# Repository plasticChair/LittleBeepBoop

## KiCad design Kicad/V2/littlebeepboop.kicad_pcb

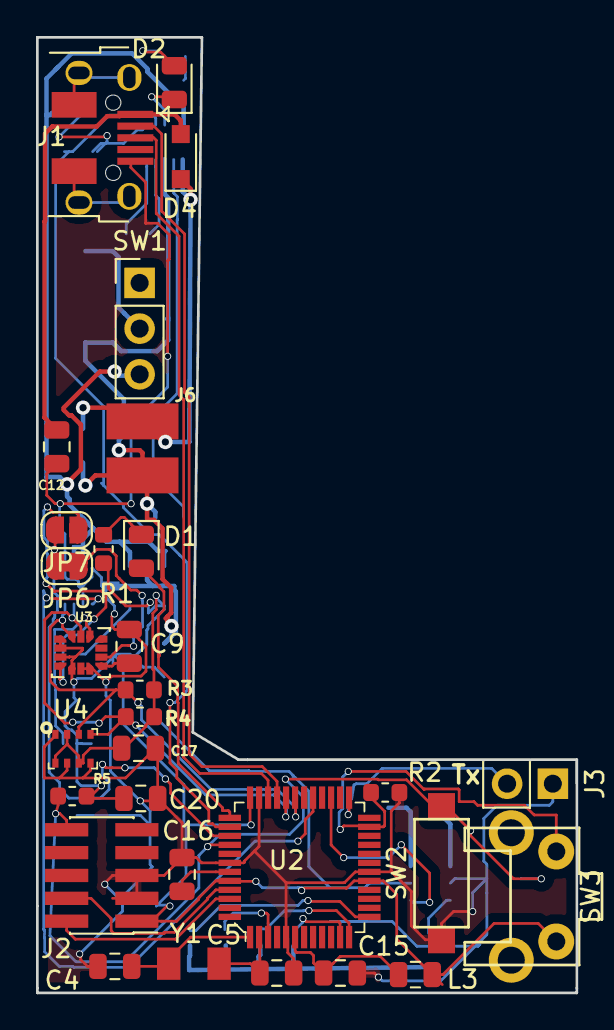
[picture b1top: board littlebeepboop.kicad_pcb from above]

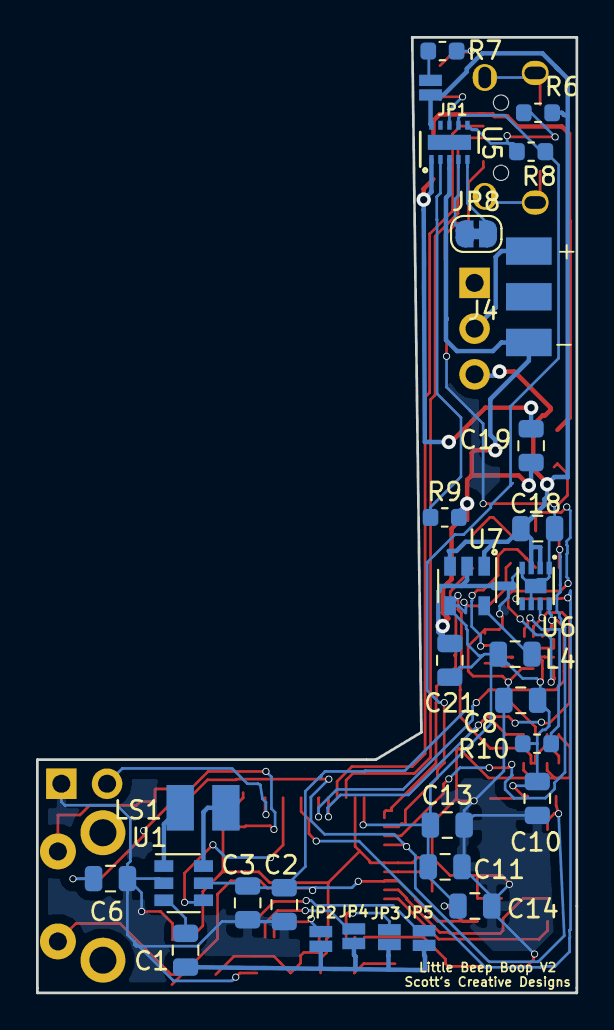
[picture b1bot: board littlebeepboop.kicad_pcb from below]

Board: 2 copper layers, 30.0 x 53.1 mm, 61 parts (31 on the bottom side), 46 nets.

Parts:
C1, C2, C3, C4, C5, C21: C; C_0805_2012Metric
C6, C10, C13, C14, C15, C16: 82n; C_0805_2012Metric
C8, C9, C12, C17, C20: 100nF; C_0805_2012Metric
C11: 2.2u; C_0805_2012Metric
C18, C19: 0.1uF; C_0805_2012Metric
D1: LED_B; LED_0805_2012Metric
D2: LED; LED_0805_2012Metric
D4: D; D_SOD-323_HandSoldering
J1: USB_B_Micro; USB_Micro-B_Adafruit
J2: Conn_ARM_JTAG_SWD_10; PinHeader_2x05_P1.27mm_Vertical_SMD
J3: Conn_01x02; PinHeader_1x02_P2.54mm_Vertical
J4: Conn_01x03; SMD_3Pin_2.54mm
J6: Conn_01x02; 2_PIN_SMD
JP1: J_NO; SMT-JUMPER_2_NO_NO-SILK
JP2, JP3, JP4, JP5: Jmp_NO; SMT-JUMPER_2_NO_NO-SILK
JP6: NC; SolderJumper-2_P1.3mm_Bridged_RoundedPad1.0x1.5mm
JP7: NO; SolderJumper-2_P1.3mm_Open_RoundedPad1.0x1.5mm
JP8: Jumper_NC_Small; SolderJumper-2_P1.3mm_Bridged_RoundedPad1.0x1.5mm
L3, L4: INDUCTOR; L_0805_2012Metric
LS1: Speaker; CMS-151125-078X
NT2: Net-Tie_2; NetTie-2_SMD_Pad0.5mm
R1: 5.6; R_0603_1608Metric
R2, R5, R6, R8, R10: 10k; R_0603_1608Metric
R3, R4: R; R_0603_1608Metric
R7: 330; R_0603_1608Metric
R9: 750; R_0603_1608Metric
SW1: SW_SPDT; PinHeader_1x03_P2.54mm_Vertical
SW2: Switch; Tact_SMD_Switch
SW3: Switch; ebay_RA_Mom_switch
U1: PAM8301; SOT-23-6
U2: ATSAMD21G18A-AUT; TQFP-48_7x7mm
U3: LSM6DS3; LGA-14_3x2.5mm_P0.5mm_LayoutBorder3x4y
U4: BMP280; LGA-8_2x2.5mm_BMP280
U5: BQ24210; WSON-10-1EP_2x3mm_P0.5mm_EP0.84x2.4mm
U6: MAX17048; TQFN-8_2x2x0.75
U7: LM3671; SOT-23-5
Y1: Crystal; TFE322P32K7680R

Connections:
/BatteryManagement/Batt-: C19.2, C21.2, J4.1, J6.2, NT2.1, R9.2, U5.3, U7.2
/BatteryManagement/Batt_int: J4.3, SW1.2
/BatteryManagement/Solar+: C19.1, D4.1, J6.1, U5.1
/RESET: C6.1, J2.10, R5.1, SW2.1, U2.40
/SWDCLK: J2.4, U2.45
/SWDIO: J2.2, U2.46
/USB_DM: J1.2, U2.33
/USB_DP: J1.3, U2.34
/VDDANA: C15.1, L3.2, U2.6
/VDDCORE: C16.1, U2.43
Audio: C1.1, JP2.1, JP3.1, JP4.1, JP5.1
BATT_ALRT: U2.29, U6.5
BattPwr: C18.2, JP1.1, R6.1, SW1.3, U5.10, U6.2, U6.3, U7.1, U7.3
BattRtn: C2.2, C3.2, C4.1, C5.1, C6.2, C8.2, C9.2, C10.2, C11.2, C12.1, C13.2, C14.2, C15.2, C16.2, C17.2, C18.1, C20.2, J1.5, J2.3, J2.5, J3.1, NT2.2, R2.2, SW2.2, U1.2, U2.5, U2.18, U2.35, U2.42, U3.6, U3.7, U4.1, U4.5, U4.7, U6.1, U6.4, U6.6, U6.9
CHRG_EN: R8.2, U2.38, U5.7
Fun_Btn_1_P23: R2.1, SW3.2, U2.23
IMU_INT: JP6.2, JP7.2, U2.39
LED1_P2: D1.2, U2.37
unnamed: C1.2, U1.3
unnamed: C4.2, U2.1, Y1.1
unnamed: C5.2, U2.2, Y1.2
unnamed: C9.1, U3.8
unnamed: D1.1, R1.1
unnamed: D2.1, U5.8
unnamed: D2.2, R7.2
unnamed: J3.2, U2.25
unnamed: JP1.2, R7.1
unnamed: JP2.2, U2.11
unnamed: JP3.2, U2.3
unnamed: JP4.2, U2.12
unnamed: JP5.2, U2.13
unnamed: JP6.1, U3.9
unnamed: JP7.1, U3.4
unnamed: JP8.1, U5.4
unnamed: JP8.2, U5.5
unnamed: L4.1, U7.5
unnamed: LS1.1, U1.6
unnamed: LS1.2, U1.1
unnamed: R6.2, R8.1, U5.6
unnamed: R9.1, U5.2
unnamed: R10.2, U3.12
SCL: R4.2, U2.32, U3.13, U4.4, U6.7
SDA: R3.2, U2.31, U3.14, U4.3, U6.8
Shutdown: U1.4, U2.27
USB_PWR: C12.2, D4.2, J1.1
Vdd: C2.1, C3.1, C8.1, C10.1, C11.1, C13.1, C14.1, C17.1, C20.1, C21.1, J2.1, L3.1, L4.2, R1.2, R3.1, R4.1, R5.2, R10.1, SW3.1, U1.5, U2.17, U2.36, U2.44, U3.1, U3.2, U3.3, U3.5, U4.2, U4.6, U4.8, U7.4

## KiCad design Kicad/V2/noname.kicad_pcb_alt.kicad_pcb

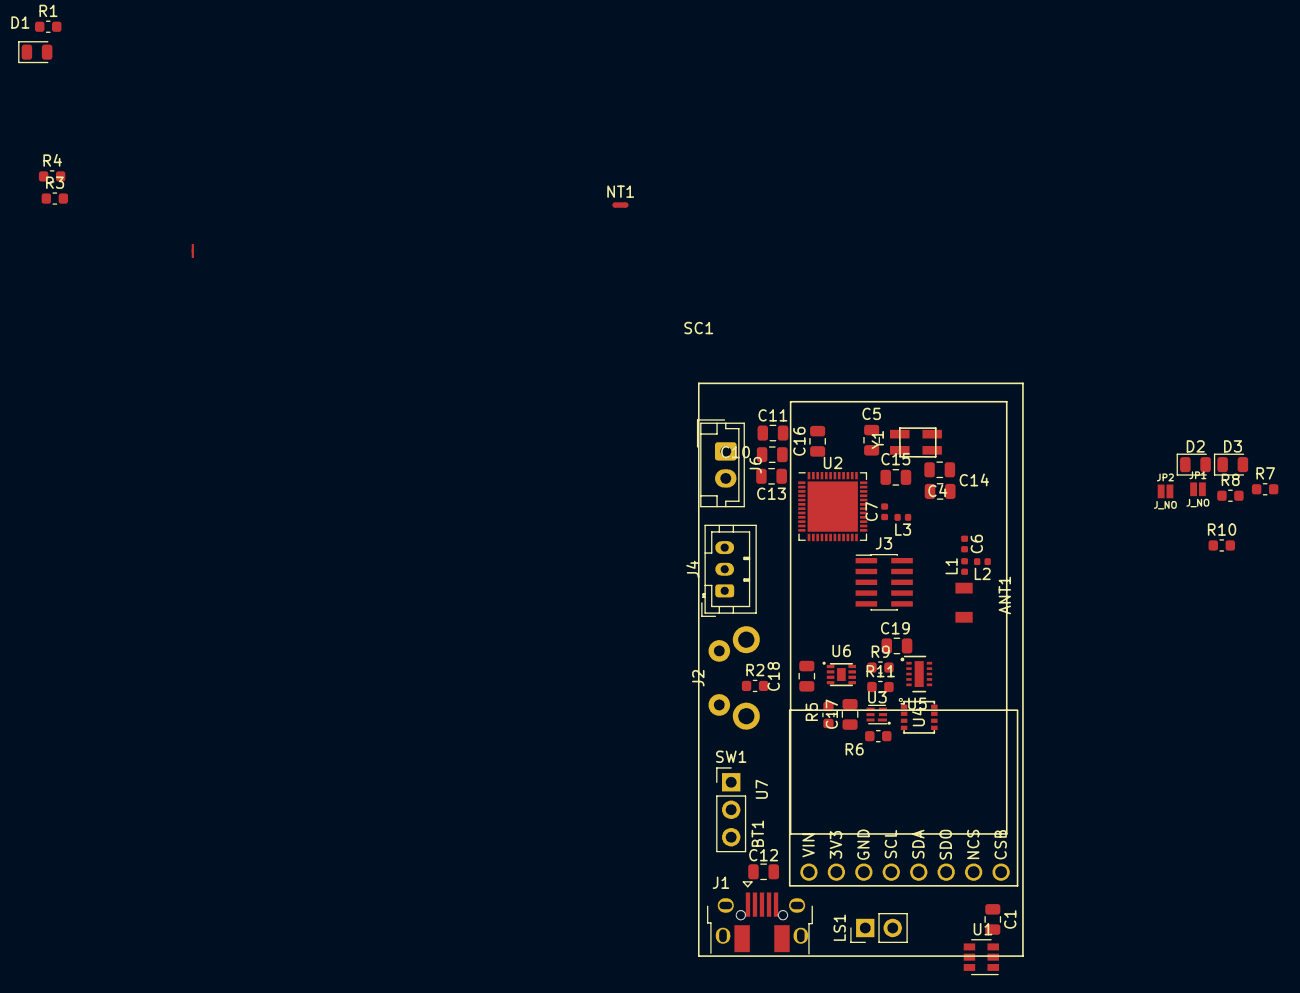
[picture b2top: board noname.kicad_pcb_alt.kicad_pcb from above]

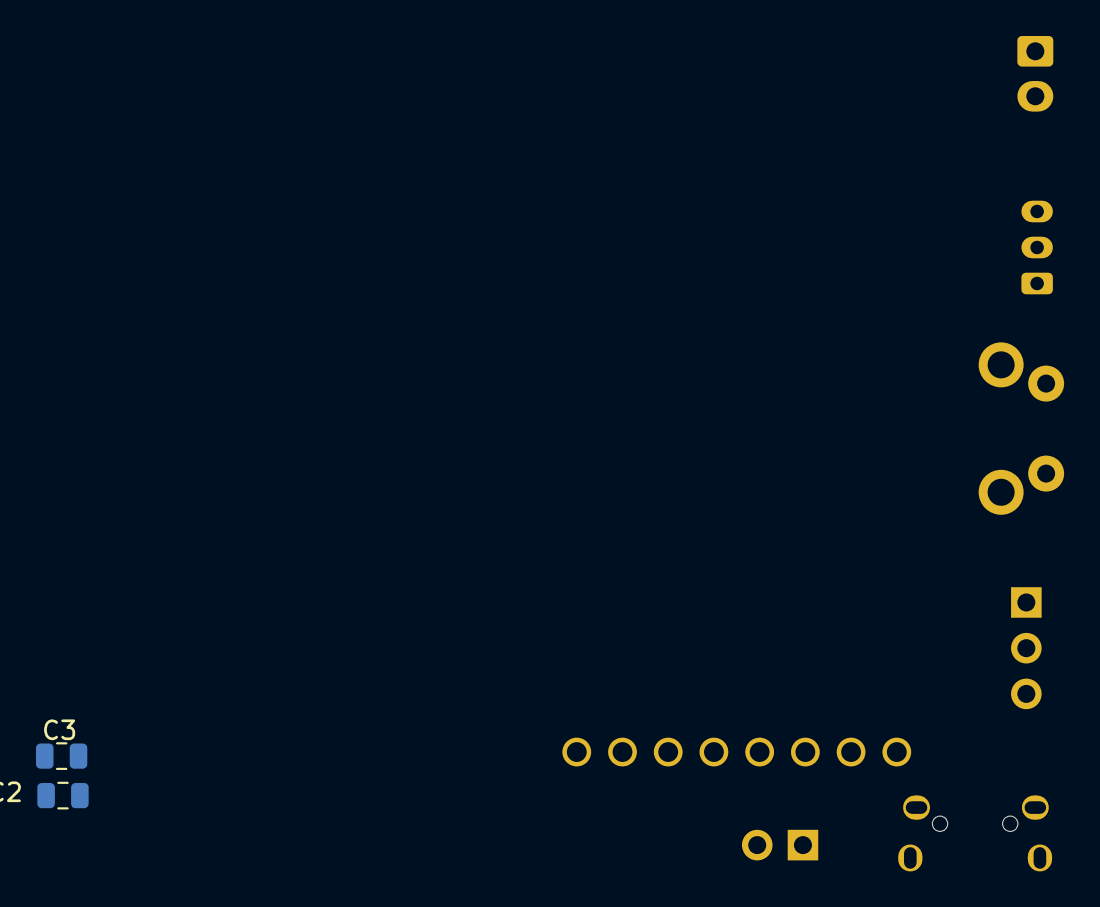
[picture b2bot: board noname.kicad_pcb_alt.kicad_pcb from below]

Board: 2 copper layers, 56 parts (2 on the bottom side), 49 nets, no tracks yet.

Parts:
ANT1: 2450AT18A100E
BT1: Battery; lipo_1cell_300mah
C1, C2, C3, C4, C5: C; C_0805_2012Metric
C6, C7: C; C_0402_1005Metric
C10, C13, C14, C15, C16: 82n; C_0805_2012Metric
C11: 2.2u; C_0805_2012Metric
C12: 100nF; C_0805_2012Metric
C17, C18, C19: 0.1uF; C_0805_2012Metric
D1: LED_B; LED_0805_2012Metric
D2, D3: LED; LED_0805_2012Metric
J1: USB_B_Micro; USB_Micro-B_Adafruit
J2: BTN1; ebay_RA_Mom_switch
J3: Conn_02x05_Odd_Even; PinHeader_2x05_P1.00mm_Vertical_SMD
J4: Conn_01x03; JST_PH_B3B-PH-K_1x03_P2.00mm_Vertical
J6: Conn_01x02; JST_EH_B02B-EH-A_1x02_P2.50mm_Vertical
JP1, JP2: J_NO; SMT-JUMPER_2_NO_NO-SILK
L1, L2, L3: INDUCTOR; L_0402_1005Metric
LS1: Speaker; PinHeader_1x02_P2.54mm_Vertical
NT1: Net-Tie_2; NetTie-2_SMD_Pad0.5mm
R1: 5.6; R_0603_1608Metric
R2: 10k; R_0603_1608Metric
R3, R4: R; R_0603_1608Metric
R5, R7, R8, R10: 330; R_0603_1608Metric
R6: 2.2k; R_0603_1608Metric
R9: 750; R_0603_1608Metric
R11: RT; R_0603_1608Metric
SC1: Solar_Cell; solarCell_53x30mm
SW1: SW_SPDT; PinHeader_1x03_P2.54mm_Vertical
U1: PAM8301; SOT-23-6
U2: nRF52832-QFxx; QFN-48-1EP_6x6mm_P0.4mm_EP4.66x4.66mm
U3: BQ297xy; WSON-6_1.5x1.5mm_P0.5mm
U4: ECH8693R; sot-28
U5: BQ24210; WSON-10-1EP_2x3mm_P0.5mm_EP0.84x2.4mm
U6: MAX17048; TQFN-8_2x2x0.75
U7: GY-91
W1: Wire_Jump; wireJump
Y1: Crystal; ECS-320-12-33Q

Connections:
/BatteryManagement/Batt+: JP1.1, JP2.1, NT1.1, R5.1, SW1.3, U5.10
/BatteryManagement/Batt-: C17.2, J4.1, U3.4, U4.1
/BatteryManagement/BattMon+: C18.2, NT1.2, U6.2, U6.3
/BatteryManagement/BattMon-: C18.1, C19.2, J6.2, R6.2, R9.2, R10.2, U4.3, U5.3, U6.1, U6.4, U6.6, U6.9
/BatteryManagement/Batt_int: J4.3, SW1.2
/BatteryManagement/NTC: J4.2, R11.2, U5.5
/BatteryManagement/Solar+: C19.1, J6.1, U5.1
/DEC1: C13.1, U2.1
/DEC2: C14.1, U2.32
/DEC3: C15.1, U2.33
/DEC4: C16.1, U2.46
/RESET: J3.10, U2.24
/SWDCLK: J3.4, U2.25
/SWDIO: J3.2, U2.26
/SWO: J3.6, U2.21
Audio: C1.1, U2.15
BattRtn: C2.2, C3.2, C4.1, C5.1, C7.2, C10.2, C11.2, C12.1, C13.2, C14.2, C15.2, C16.2, J1.5, J3.3, J3.5, J3.9, L2.1, R2.2, U1.2, U2.31, U2.45, U2.49, U7.3
Fun_Btn_1_P23: J2.1, R2.1, U2.8
LED1_P2: D1.2, U2.7
unnamed: ANT1.1, L1.1
unnamed: C1.2, U1.3
unnamed: C4.2, U2.34, Y1.1
unnamed: C5.2, U2.35, Y1.2
unnamed: C6.1, L3.1
unnamed: C6.2, L1.2, L2.2
unnamed: C7.1, L3.2, U2.30
unnamed: C17.1, R5.2, U3.5
unnamed: D1.1, R1.1
unnamed: D2.1, U5.8
unnamed: D2.2, R7.2
unnamed: D3.1, U5.6, U5.7
unnamed: D3.2, R8.2
unnamed: JP1.2, R7.1
unnamed: JP2.2, R8.1
unnamed: LS1.1, U1.6
unnamed: LS1.2, U1.1
unnamed: R6.1, W1.1
unnamed: R9.1, U5.2
unnamed: R10.1, U5.9
unnamed: R11.1, U5.4
unnamed: U3.2, U4.4
unnamed: U3.3, U4.2
unnamed: U3.6, W1.2
unnamed: U4.5, U4.6, U4.7, U4.8
SCL: R4.2, U2.10, U7.4
SDA: R3.2, U2.9, U7.5
Shutdown: U1.4, U2.17
USB_PWR: C12.2, J1.1
Vdd: C2.1, C3.1, C10.1, C11.1, J2.2, J3.1, R1.2, R3.1, R4.1, U1.5, U2.13, U2.36, U2.47, U2.48, U7.1

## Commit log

2019-05-16 init git
2019-06-30 Multi project updates
